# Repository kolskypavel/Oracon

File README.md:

# Oracon
Orienteering radio control using NB-Iot SIM7028 module and ESP32S3. Originally a bachelor thesis for FIT CTU.

## Technologies
- **Gate** - Spring boot, PostgreSQL
- **End devices** - PlatformIO, C++

## Hardware
- Custom made PCB with a LiPol battery and custom case.

## SI compatibility
- SI BSF 7 stations with RS232 or USB
- SI SRR dongle
- SI SRR module to be implemented

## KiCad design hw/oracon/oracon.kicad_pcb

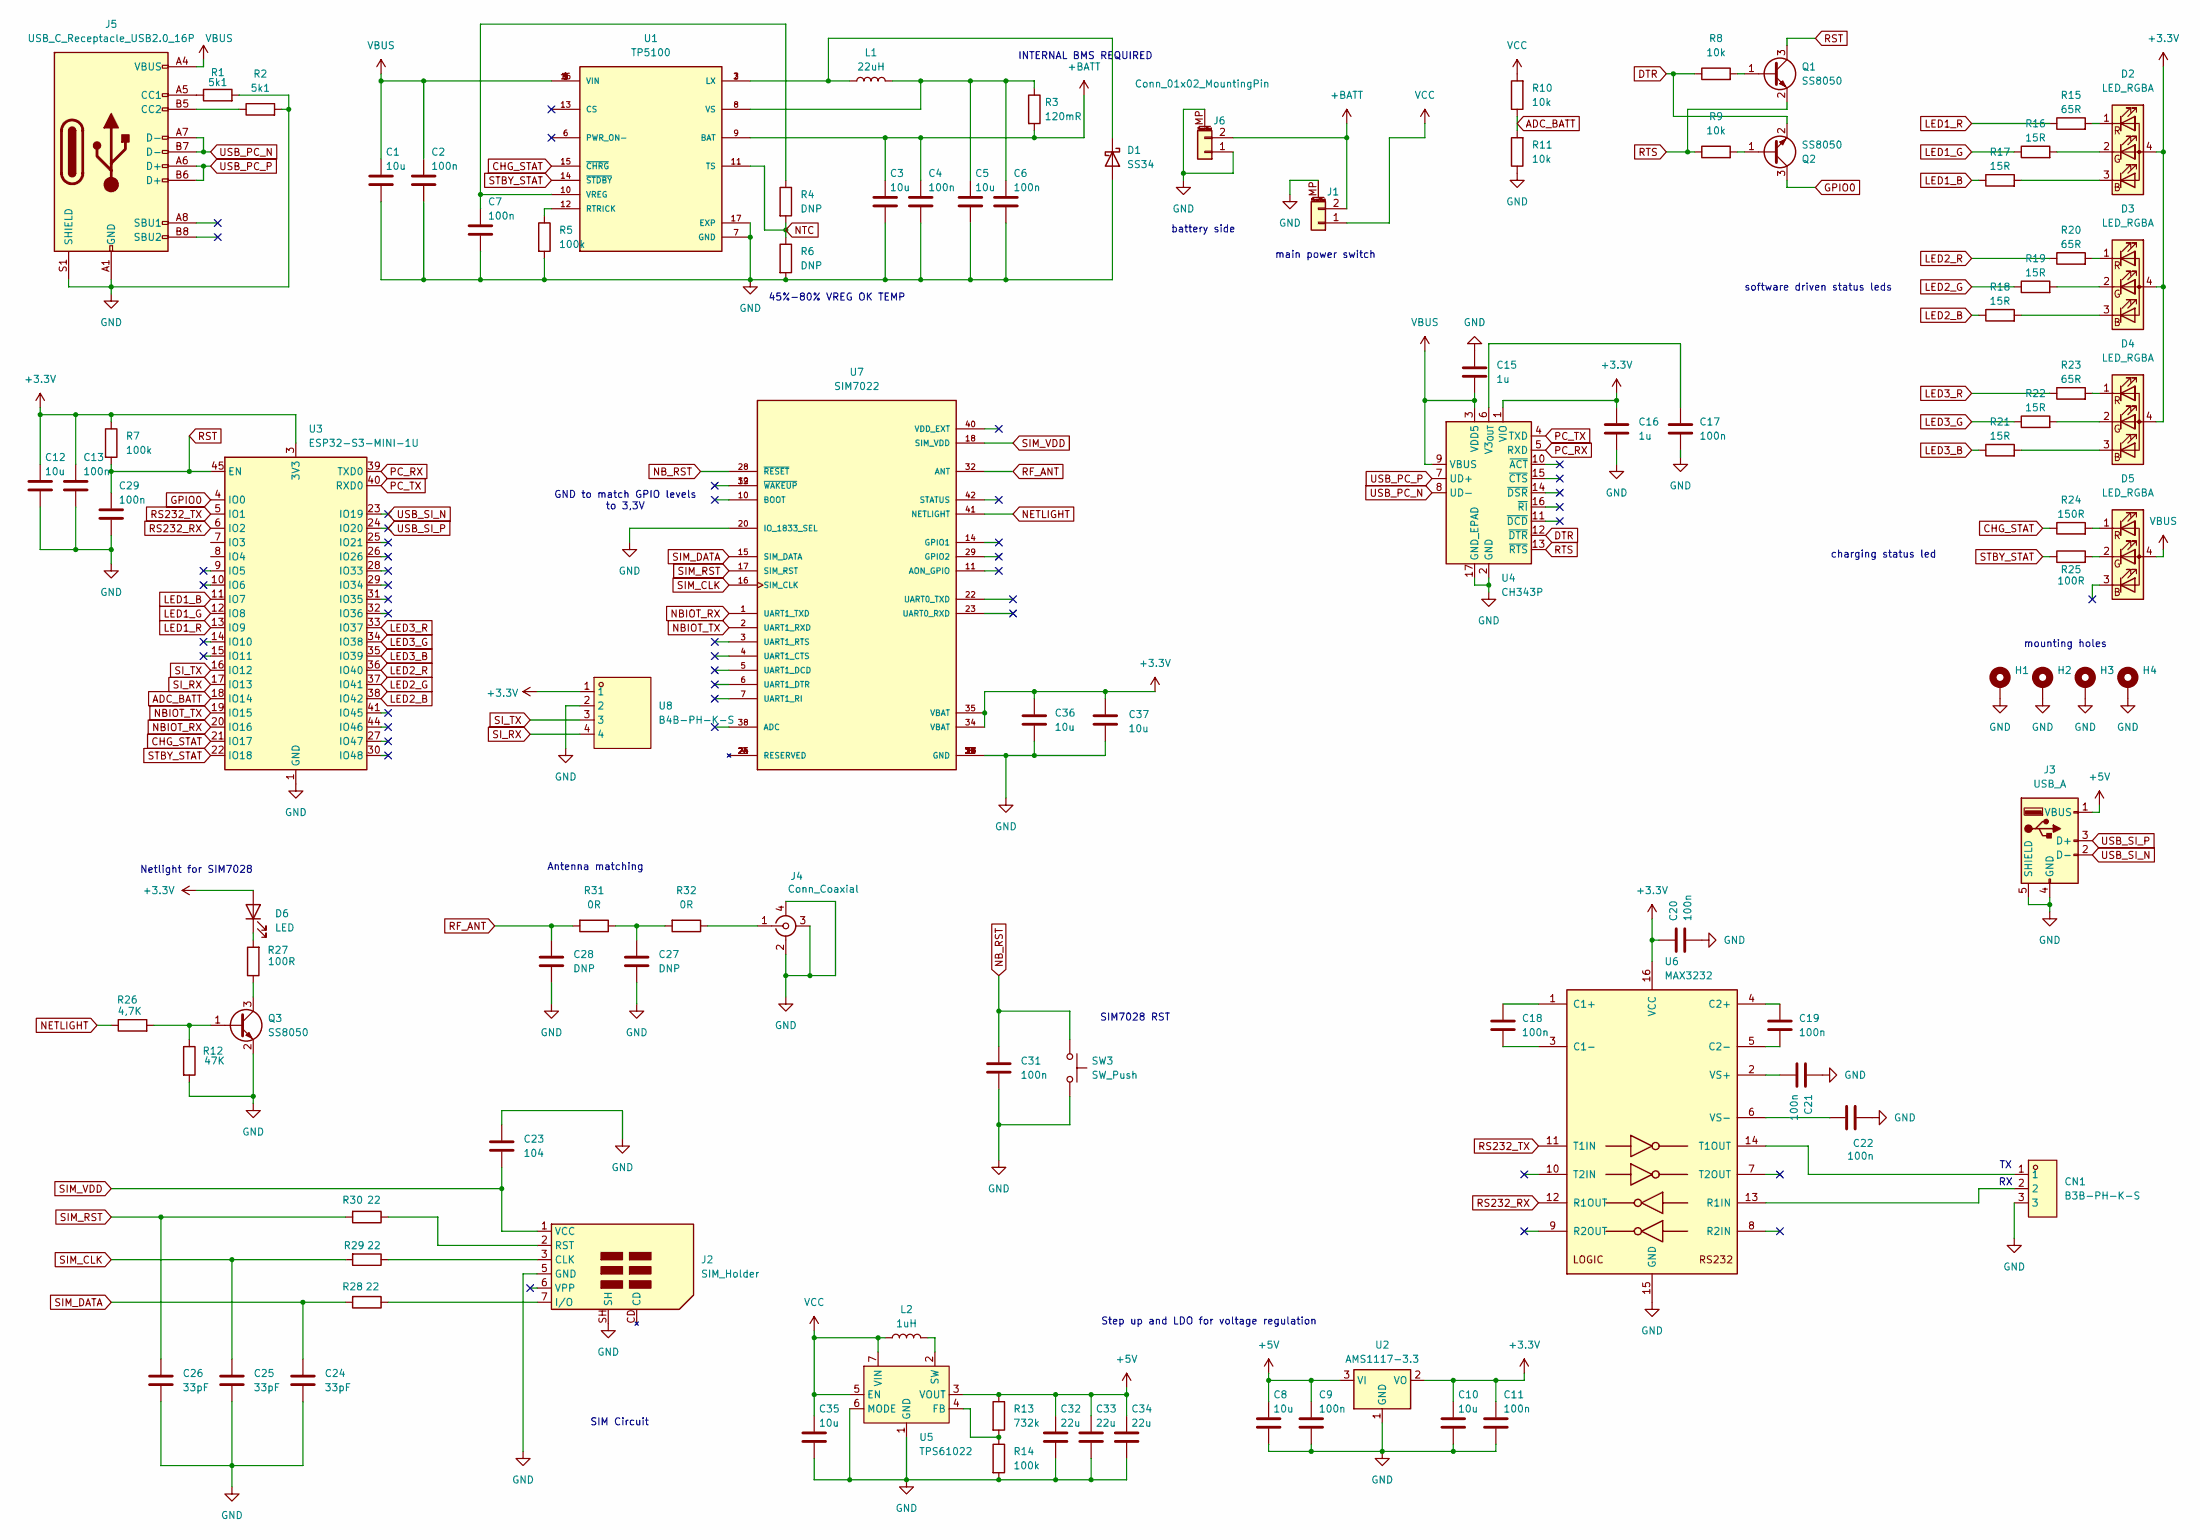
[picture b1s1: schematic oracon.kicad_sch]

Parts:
C1, C3, C5, C8, C10, C12, C35, C36, C37: 10u; C_0805_2012Metric; MPN C1713; lcsc C15850
C2, C4, C6, C7, C9, C11, C13, C17, C18, C19, C20, C21, C22, C29: 100n; C_0402_1005Metric; MPN C77020; lcsc C5137468
C15, C16: 1u; C_0603_1608Metric; lcsc C6119852
C23: 104; C_0603_1608Metric; lcsc C14663
C24, C25, C26: 33pF; C_0402_1005Metric; lcsc C1562
C27, C28: DNP; C_0402_1005Metric
C31: 100n; C_0402_1005Metric; lcsc C5137468
C32, C33, C34: 22u; C_0805_2012Metric; MPN C98190; lcsc C5674
CN1: B3B-PH-K-S; CONN-TH_B3B-PH-K-S; MPN B3B-PH-K-S(LF)(SN); LCSC Part C131339
D1: SS34; D_SMA; MPN C8678; lcsc C8678
D2, D3, D4, D5: LED_RGBA; LED_RGB_1210; lcsc C2827321
D6: LED; LED_0603_1608Metric; lcsc C19171390
H1, H2, H3, H4: MountingHole_Pad; MountingHole_3.2mm_M3_DIN965_Pad
J1, J6: Conn_01x02_MountingPin; CONN-TH_B2B-PH-K-S; lcsc C131337
J2: SIM_Holder; nanoSIM_Hinged_CUI_NSIM-2-C; lcsc C2962044
J3: USB_A; HYC214-USBA04-113; lcsc C3034180
J4: Conn_Coaxial; IPEX-SMD_4P-L1.8-W1.7-LS2.0; lcsc C41432125
J5: USB_C_Receptacle_USB2.0_16P; HOAUC HYCW412-USBC16-065B; lcsc C5342196
L1: 22uH; CYA0630; MPN C5189960; lcsc C5189960
L2: 1uH; CYA0630; MPN C5189744; lcsc C5189744
Q1, Q2, Q3: SS8050; SOT-23; MPN C2150; lcsc C2150
R1, R2: 5k1; R_0402_1005Metric; MPN C23186; lcsc C25905
R3: 120mR; R_1206_3216Metric; MPN C7467250; lcsc C24435
R4, R6: DNP; R_0402_1005Metric; MPN C25741
R5, R7, R14: 100k; R_0402_1005Metric; MPN C25741; lcsc C60491
R8, R9, R10, R11: 10k; R_0402_1005Metric; MPN C25531; lcsc C60490
R12: 47K; R_0402_1005Metric; lcsc C25792
R13: 732k; R_0402_1005Metric; MPN C27016; lcsc C5159692
R15, R20, R23: 65R; R_0402_1005Metric; lcsc C3016024
R16, R17, R18, R19, R21, R22: 15R; R_0402_1005Metric; lcsc C2909323
R24: 150R; R_0402_1005Metric; lcsc C25082
R25, R27: 100R; R_0402_1005Metric; lcsc C25076
R26: 4,7K; R_0402_1005Metric; lcsc C25900
R28, R29, R30: 22; R_0402_1005Metric; lcsc C25092
R31, R32: 0R; R_0402_1005Metric; lcsc C106231
SW3: SW_Push; SW_SPST_TS-1088-xR020; lcsc C720477
U1: TP5100; QFN-16-1EP_4x4mm_P0.65mm_EP2.1x2.1mm; MPN C379389; lcsc C379389
U2: AMS1117-3.3; SOT-223-3_TabPin2; lcsc C347222
U3: ESP32-S3-MINI-1U; ESP32-S2-MINI-1U; lcsc C2980299
U4: CH343P; WCH_QFN-16-1EP_3x3mm_P0.5mm_EP1.8x1.8mm; lcsc C2846043
U5: TPS61022; Texas_RWU0007A_VQFN-7_2x2mm_P0.5mm; MPN C915088; lcsc C915088
U6: MAX3232; SOIC-16_3.9x9.9mm_P1.27mm; lcsc C19268179
U7: SIM7022; SIMCOM_SIM7022; PARTREV V1.00; lcsc C7363803
U8: B4B-PH-K-S; CONN-TH_B4B-PH-K-S; MPN B4B-PH-K-S(LF)(SN); LCSC Part C131334

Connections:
+3.3V: C10.1, C11.1, C12.1, C13.1, C16.1, C20.1, C36.1, C37.1, D2.4 (A), D3.4 (A), D4.4 (A), D6.2 (A), R7.1, U2.2 (VO), U3.3 (3V3), U4.1 (VIO), U6.16 (VCC), U7.34 (VBAT), U7.35 (VBAT), U8.1
+5V: C8.1, C9.1, C32.1, C33.1, C34.1, J3.1 (VBUS), R13.1, U2.3 (VI), U5.3 (VOUT)
+BATT: C3.1, C4.1, J1.2, J6.2, R3.2, U1.9 (BAT)
ADC_BATT: R10.1, R11.2, U3.18 (IO14)
CHG_STAT: R24.1, U1.15 (~CHRG), U3.21 (IO17)
DTR: Q2.2 (E), R8.1, U4.12 (~DTR)
GND: C1.2, C2.2, C3.2, C4.2, C5.2, C6.2, C7.2, C8.2, C9.2, C10.2, C11.2, C12.2, C13.2, C15.1, C16.2, C17.2, C20.2, C21.1, C22.1, C23.1, C24.2, C25.2, C26.2, C27.2, C28.2, C29.2, C31.2, C32.2, C33.2, C34.2, C35.2, C36.2, C37.2, CN1.3, D1.2 (A), H1.1, H2.1, H3.1, H4.1, J1.MP (MountPin), J2.5 (GND), J2.SH, J3.4 (GND), J3.5 (SHIELD), J4.2 (Ext), J4.3 (Ext), J4.4 (Ext), J5.A1 (GND), J5.A12 (GND), J5.B1 (GND), J5.B12 (GND), J5.S1 (SHIELD), J6.1, J6.MP (MountPin), Q3.2 (E), R1.2, R2.2, R5.2, R6.2, R11.1, R12.2, R14.2, SW3.2, U1.7 (GND), U1.17 (EXP), U2.1 (GND), U3.1 (GND), U3.2 (GND), U3.42 (GND), U3.43 (GND), U3.46 (GND), U3.47 (GND), U3.48 (GND), U3.49 (GND), U3.50 (GND), U3.51 (GND), U3.52 (GND), U3.53 (GND), U3.54 (GND), U3.55 (GND), U3.56 (GND), U3.57 (GND), U3.58 (GND), U3.59 (GND), U3.60 (GND), U3.61 (GND), U3.62 (GND), U3.63 (GND), U3.64 (GND), U3.65 (GND), U4.2 (GND), U4.17 (GND_EPAD), U5.1 (GND), U5.6 (MODE), U6.15 (GND), U7.8 (GND), U7.13 (GND), U7.19 (GND), U7.20 (IO_1833_SEL), U7.21 (GND), U7.27 (GND), U7.30 (GND), U7.31 (GND), U7.33 (GND), U7.36 (GND), U7.37 (GND), U8.2
GPIO0: Q2.3 (C), U3.4 (IO0)
LED1_B: R17.1, U3.11 (IO7)
LED1_G: R16.1, U3.12 (IO8)
LED1_R: R15.1, U3.13 (IO9)
LED2_B: R18.1, U3.38 (IO42)
LED2_G: R19.1, U3.37 (IO41)
LED2_R: R20.1, U3.36 (IO40)
LED3_B: R21.1, U3.35 (IO39)
LED3_G: R22.1, U3.34 (IO38)
LED3_R: R23.1, U3.33 (IO37)
NBIOT_RX: U3.20 (IO16), U7.1 (UART1_TXD)
NBIOT_TX: U3.19 (IO15), U7.2 (UART1_RXD)
NB_RST: C31.1, SW3.1, U7.28 (~RESET)
NETLIGHT: R26.1, U7.41 (NETLIGHT)
NTC: R4.2, R6.1, U1.11 (TS)
unnamed: C27.1, R31.1, R32.2
unnamed: D1.1 (K), L1.1, U1.2 (LX), U1.3 (LX)
unnamed: D2.3 (BK), R17.2
unnamed: D2.2 (GK), R16.2
unnamed: D2.1 (RK), R15.2
unnamed: D3.3 (BK), R18.2
unnamed: D3.2 (GK), R19.2
unnamed: D3.1 (RK), R20.2
unnamed: D4.3 (BK), R21.2
unnamed: D4.2 (GK), R22.2
unnamed: D4.1 (RK), R23.2
unnamed: D5.2 (GK), R25.2
unnamed: D5.1 (RK), R24.2
unnamed: D6.1 (K), R27.2
unnamed: J2.3 (CLK), R29.1
unnamed: J2.7 (I/O), R28.1
unnamed: J2.2 (RST), R30.1
unnamed: J4.1 (In), R32.1
unnamed: J5.A5 (CC1), R1.1
unnamed: J5.B5 (CC2), R2.1
unnamed: Q1.1 (B), R8.2
unnamed: Q2.1 (B), R9.2
unnamed: Q3.1 (B), R12.1, R26.2
unnamed: Q3.3 (C), R27.1
unnamed: R5.1, U1.12 (RTRICK)
unnamed: C7.1, R4.1, U1.10 (VREG)
unnamed: C5.1, C6.1, L1.2, R3.1, U1.8 (VS)
unnamed: C17.1, U4.6 (V3_{OUT})
unnamed: R13.2, R14.1, U5.4 (FB)
unnamed: L2.2, U5.2 (SW)
unnamed: C18.1, U6.1 (C1+)
unnamed: C18.2, U6.3 (C1-)
unnamed: C19.1, U6.4 (C2+)
unnamed: C19.2, U6.5 (C2-)
unnamed: CN1.2, U6.13 (R1IN)
unnamed: CN1.1, U6.14 (T1OUT)
unnamed: C21.2, U6.2 (VS+)
unnamed: C22.2, U6.6 (VS-)
PC_RX: U3.39 (TXD0), U4.5 (RXD)
PC_TX: U3.40 (RXD0), U4.4 (TXD)
RF_ANT: C28.1, R31.2, U7.32 (ANT)
RS232_RX: U3.6 (IO2), U6.12 (R1OUT)
RS232_TX: U3.5 (IO1), U6.11 (T1IN)
RST: C29.1, Q1.3 (C), R7.2, U3.45 (EN)
RTS: Q1.2 (E), R9.1, U4.13 (~RTS)
SIM_CLK: C25.1, R29.2, U7.16 (SIM_CLK)
SIM_DATA: C24.1, R28.2, U7.15 (SIM_DATA)
SIM_RST: C26.1, R30.2, U7.17 (SIM_RST)
SIM_VDD: C23.2, J2.1 (VCC), U7.18 (SIM_VDD)
SI_RX: U3.17 (IO13), U8.4
SI_TX: U3.16 (IO12), U8.3
STBY_STAT: R25.1, U1.14 (~STDBY), U3.22 (IO18)
USB_PC_N: J5.A7 (D-), J5.B7 (D-), U4.8 (UD-)
USB_PC_P: J5.A6 (D+), J5.B6 (D+), U4.7 (UD+)
USB_SI_N: J3.2 (D-), U3.23 (IO19)
USB_SI_P: J3.3 (D+), U3.24 (IO20)
VBUS: C1.1, C2.1, C15.2, D5.4 (A), J5.A4 (VBUS), J5.A9 (VBUS), J5.B4 (VBUS), J5.B9 (VBUS), U1.1 (VIN), U1.4 (VIN), U1.5 (VIN), U1.16 (VIN), U4.3 (VDD5), U4.9 (VBUS)
VCC: C35.1, J1.1, L2.1, R10.2, U5.5 (EN), U5.7 (VIN)

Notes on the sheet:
battery side
mounting holes
SIM7028 RST
SIM Circuit
software driven status leds
main power switch
45%-80% VREG OK TEMP
INTERNAL BMS REQUIRED
GND to match GPIO levels to 3,3V
Step up and LDO for voltage regulation
charging status led
Antenna matching
Netlight for SIM7028

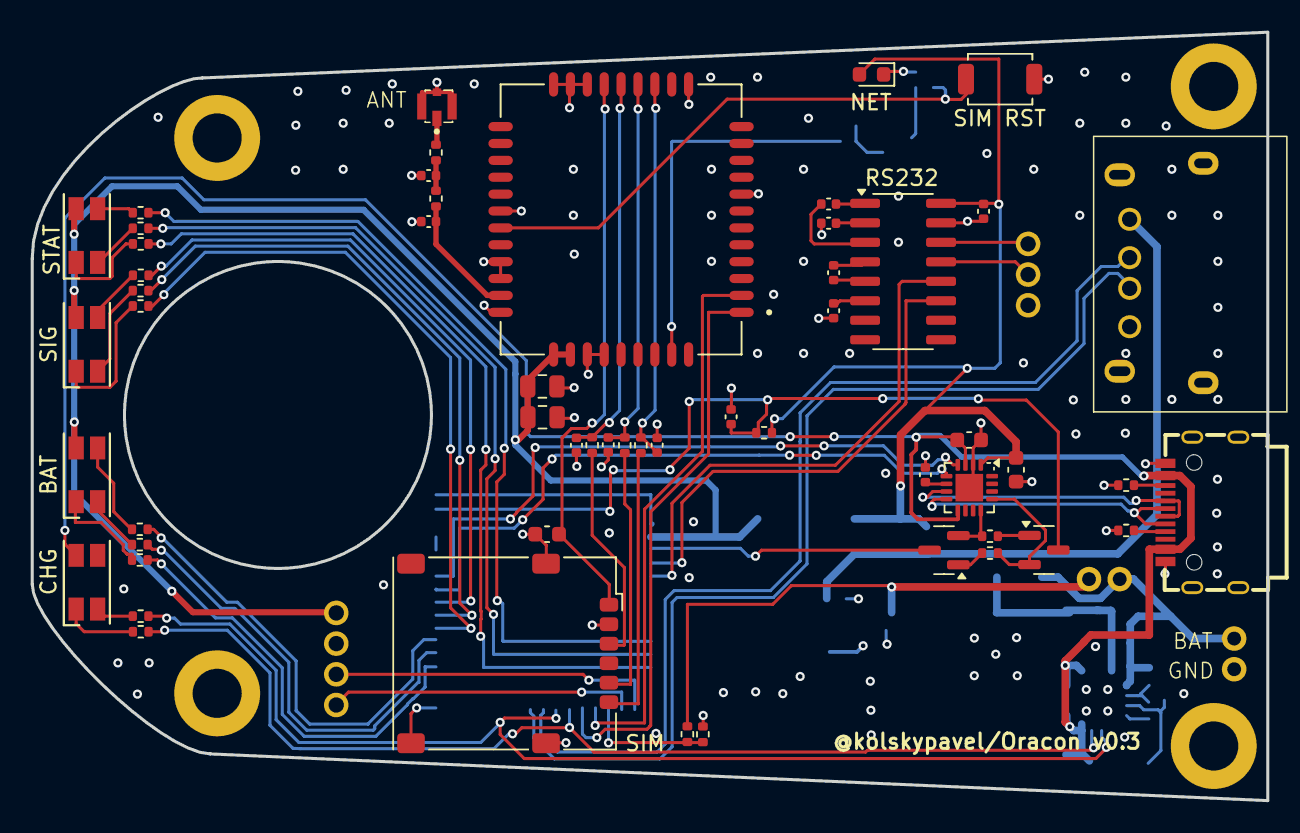
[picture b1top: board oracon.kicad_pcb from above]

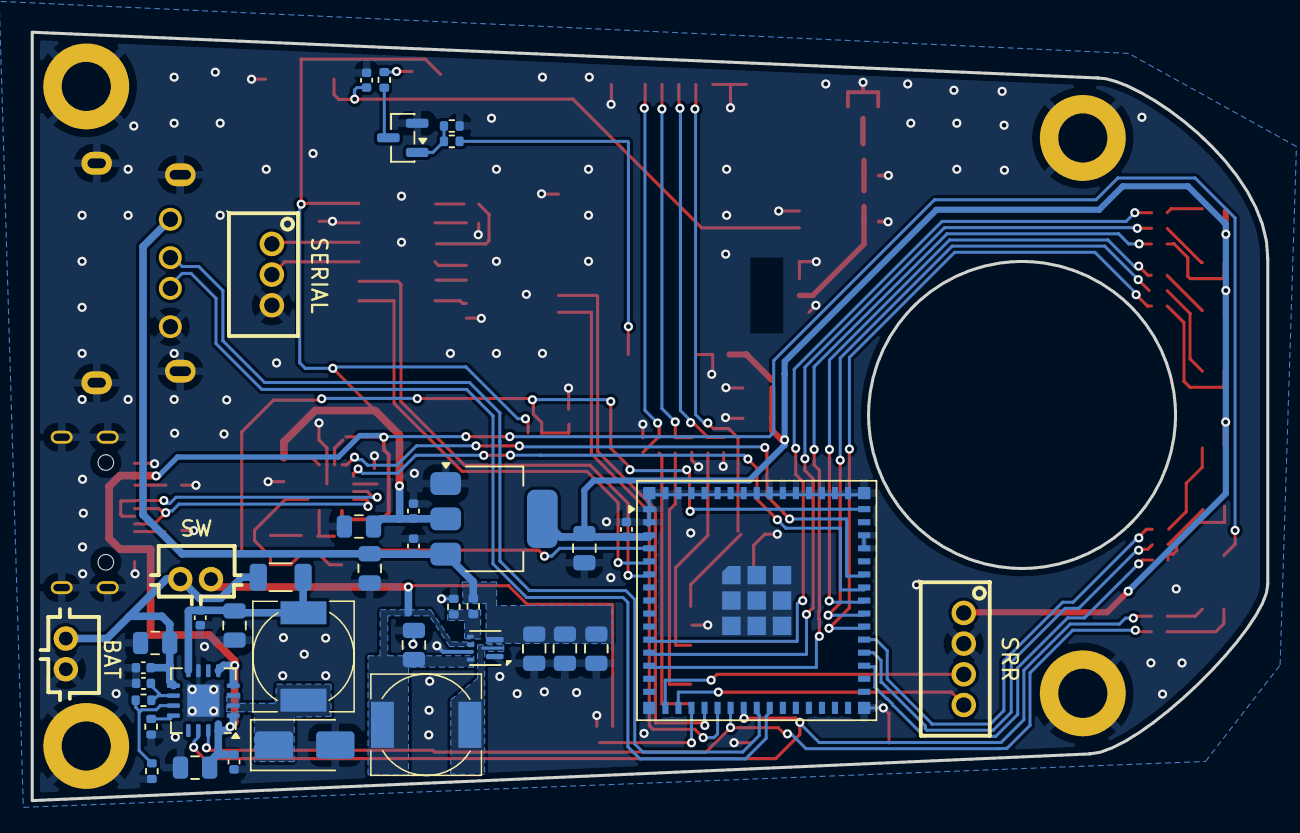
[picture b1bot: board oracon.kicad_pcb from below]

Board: 4 copper layers, 80.5 x 50.1 mm, 98 parts (39 on the bottom side), 80 nets.

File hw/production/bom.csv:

Designator,Footprint,Quantity,Value,LCSC Part #
"C1, C10, C12, C14, C3, C35, C5, C8",0805,8,10u,C1713
"C11, C13, C17, C18, C19, C2, C20, C21, C22, C4, C6, C7, C9",0402,13,100n,C77020
"C15, C16",0603,2,1u,
"C32, C33, C34",0805,3,22u,C98190
D1,D_SMA,1,SS34,C8678
"D2, D3, D4, D5",LED_RGB_1210,4,LED_RGBA,
J1,DSUB-9_Pins_Horizontal_P2.77x2.84mm_EdgePinOffset4.94mm_Housed_MountingHolesOffset4.94mm,1,DE9_Pins_MountingHoles,
J3,USB_A_Molex_67643_Horizontal,1,USB_A,
J4,PinHeader_2x20_P2.54mm_Vertical,1,Conn_02x20_Odd_Even,
J5,USB_C_Receptacle_GCT_USB4105-xx-A_16P_TopMnt_Horizontal,1,USB_C_Receptacle_USB2.0_16P,
L1,CYA0630,1,22uH,C5189960
L2,CYA0630,1,1uH,C5189744
"Q1, Q2",SOT-23,2,SS8050,C2150
"R1, R2",0402,2,5k1,C23186
"R10, R11, R8, R9",0402,4,10k,C25531 
"R12, R14, R5, R7",0402,4,100k,C25741
R13,0402,1,732k,C27016
"R15, R20, R23",0402,3,65R,
"R16, R17, R18, R19, R21, R22",0402,6,15R,
R24,0402,1,150R,
R25,0402,1,100R,
R3,1206,1,0R1,C7467250
"R4, R6",0402,2,x,C25741
TP1,TestPoint_Pad_D1.5mm,1,BATT,
TP2,TestPoint_Pad_D1.5mm,1,GND,
TP3,TestPoint_Pad_D1.5mm,1,SW1,
TP4,TestPoint_Pad_D1.5mm,1,SW4,
U1,QFN-16-1EP_4x4mm_P0.65mm_EP2.1x2.1mm,1,TP5100,C379389
U2,SOT-223-3_TabPin2,1,AMS1117-3.3,
U3,ESP32-S2-MINI-1U,1,ESP32-S3-MINI-1U,
U4,WCH_QFN-16-1EP_3x3mm_P0.5mm_EP1.8x1.8mm,1,CH343P,
U5,Texas_RWU0007A_VQFN-7_2x2mm_P0.5mm,1,TPS61022,C915088
U6,SOIC-16_3.9x9.9mm_P1.27mm,1,MAX3232,

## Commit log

2025-03-20 sync current state of project
2025-03-20 DS_Store files removed
2025-04-08 goofy midnight commit
2025-04-09 Structure, messages, parsers - initial
2025-04-10 Encryptor, parser, commands, cleanups
2025-04-11 Protocol + socket work
2025-04-11 Further parsing and socket processing - needs to be fixed
2025-04-12 Changed control logic to exceptions, parser + protocol work, receive of punches needs to be fixed
2025-04-13 Status timers, parsing, queue receive
2025-04-14 Demo init, key parsing, run status
2025-04-14 Replay counter removed (TCP handles)
2025-04-15 Added debug, socket connection (to be tested), loading keys OK
2025-04-16 Serial read and write modified, si parser changed, commands need to be updated
2025-04-16 Updated serial commands and some serial init logic - needs to be fixed
2025-04-16 RS232 task, data receive updated
2025-04-16 Fixed serial write
2025-04-17 Socket work, bugfixes, parsing
2025-04-17 Signature generation changes + tests, to be fixed
2025-04-17 Padding, still buggy encryption
2025-04-18 Mesage bugfixes, protocol work
2025-04-19 BP: further logs, socket check before opening, manual buffered reading from socket (buggy) + init rs232 read task
2025-04-20 Fixed reading from rs232 serial
2025-04-21 Fixed long message retrieval, parsing messages, some debug
2025-04-22 Create README.md
    File cleanup
2025-04-22 File cleanup, restruct
2025-04-23 Reading and setting config messages
2025-04-24 Modified crypto test + small changes for USB task
2025-04-27 Fixed the encryptor tests, cleanup + comments on defines
2025-04-27 To be fixed: work on rsa version
2025-04-28 Modified encryption, changed tests
2025-04-29 Some RSA work, non functional
2025-04-29 misc updates
2025-04-30 Changed to initial AES/RSA hybrid, bugfixes
2025-05-01 Punch sending fixed, parameter tweaks
2025-05-02 Queue backup using filesystem
2025-05-02 Queue bugfixes - flush workaround
2025-05-03 LEDs + queue cleanup
2025-05-03 Task wdt fixed, init moved, LED work
2025-05-04 Bugfixes, small socket changes
2025-05-05 Added SI parsing verification, fixed USB mem corruption
2025-05-09 Defines cleanup + comments
2025-05-10 Cleanup
2025-09-13 initial work on http, not functioning
2025-10-01 work on http, now compiling
2025-10-02 modified for non HAT
2025-10-03 further http work
2025-10-03 hw: further work on PCB
2025-10-04 Work on PCB, renamed KiCad project
2025-10-05 PCB layout - init
2025-10-05 PCB work, back to basics :D
2025-10-06 Further PCB work
2025-10-07 Further PCB work - almost ready
2025-10-08 PCB work, paths and zones
2025-10-08 Some PCB restruct
2025-10-09 Rerouted some ESP pins
2025-10-10 Further routing
2025-10-13 Moved charging LED to green channel
2025-10-13 Unconnected schema fix
2025-10-14 Changed to 4 layer PCB
2025-10-14 Finished work with GND
2025-10-16 fixed vias
2025-10-16 check
2025-10-16 via stiching
2025-10-17 finishing before ordering
2025-11-20 CSQ fix, hw work, cleanup
2025-11-26 made pcb smaller, work to be done
2025-11-29 To be checked for production.
2026-04-20 added connectors, USB + dimensions to be checked
2026-04-22 usb position modifications
2026-05-07 modified for multiple punch acceptance, bugfixes
2026-05-17 fixed backup reading
